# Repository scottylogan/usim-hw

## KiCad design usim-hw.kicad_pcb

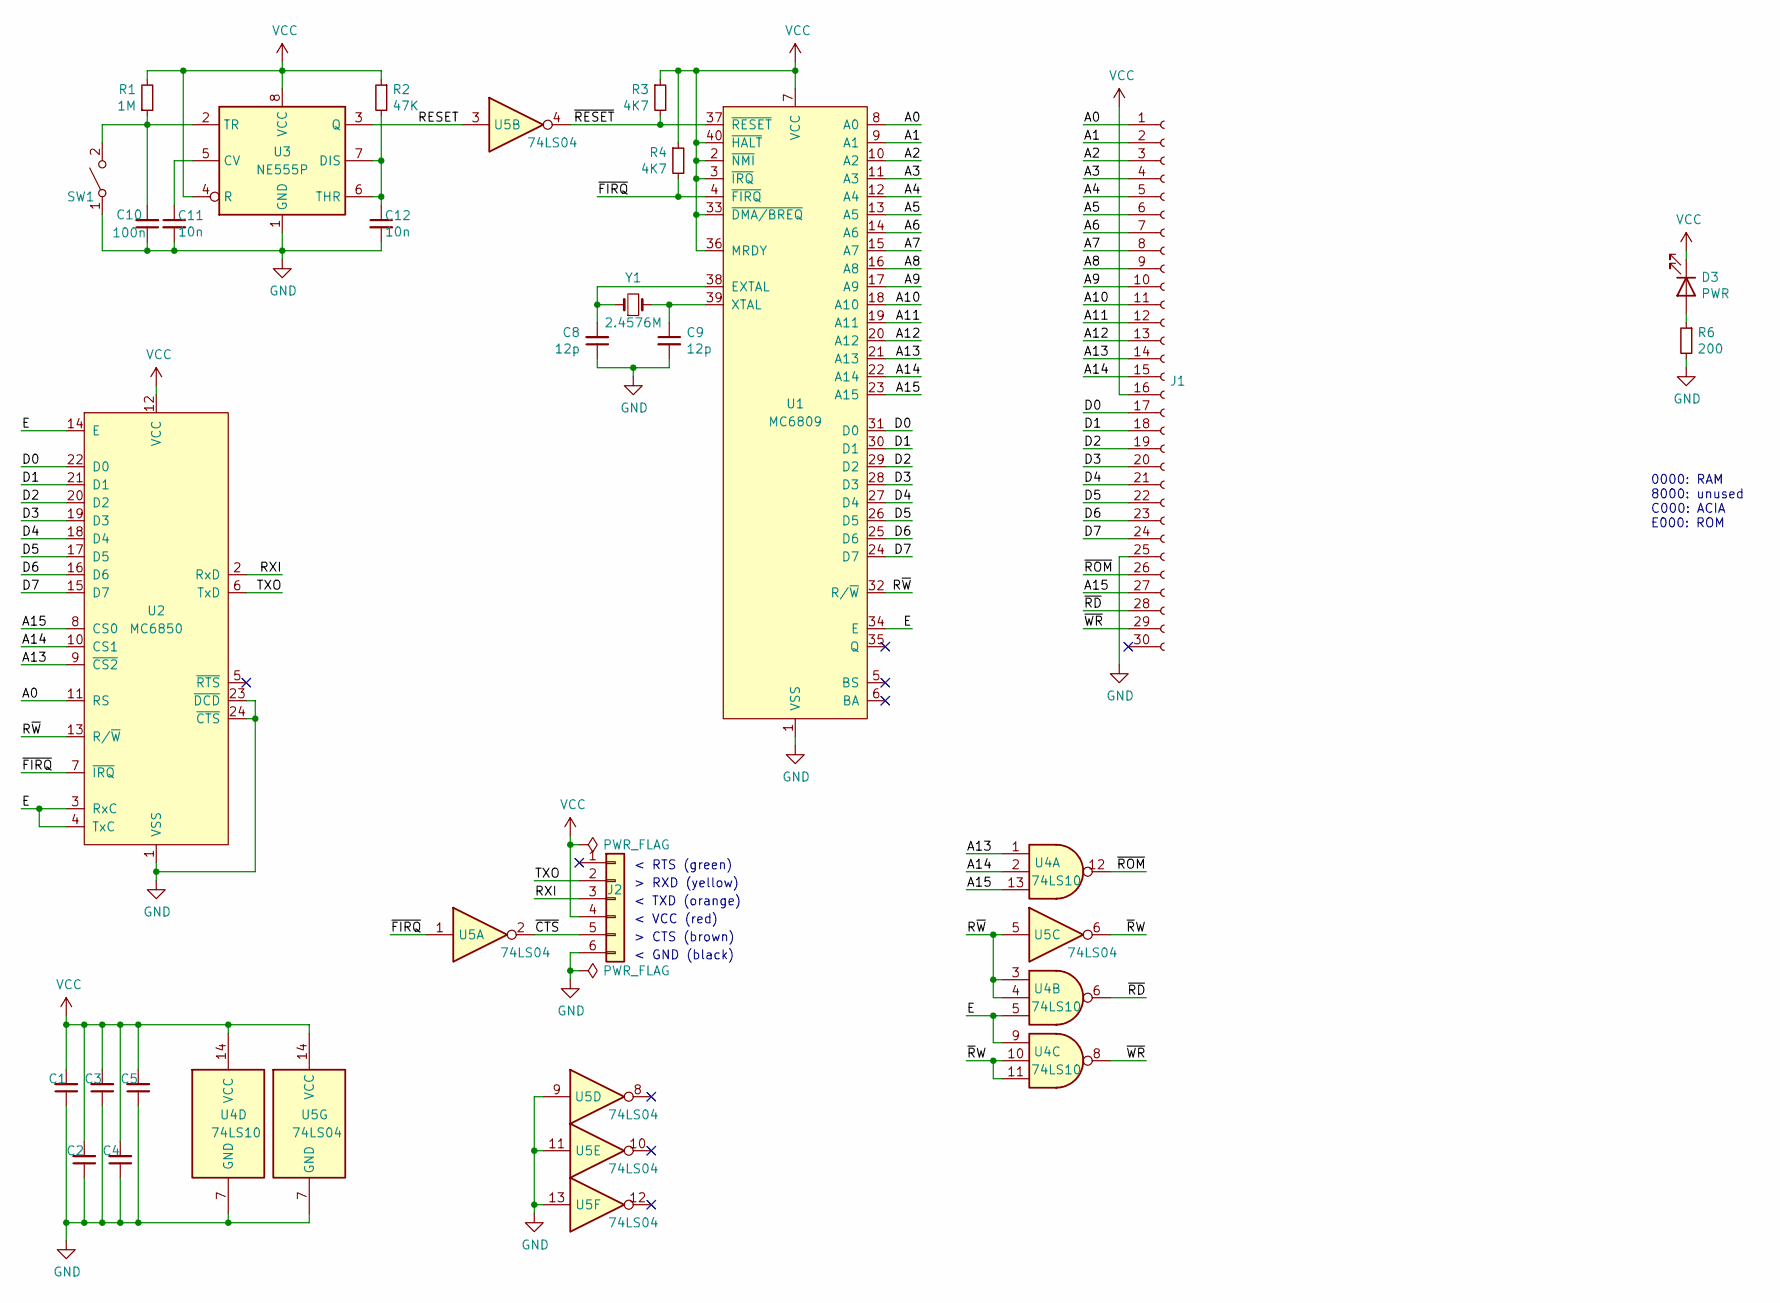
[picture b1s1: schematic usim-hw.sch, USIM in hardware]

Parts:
C1, C2, C3, C4, C5, C10: 100n; C_Disc_D3.0mm_W1.6mm_P2.50mm
C8, C9: 12p; C_Disc_D3.0mm_W1.6mm_P2.50mm
C11, C12: 10n; C_Disc_D3.0mm_W1.6mm_P2.50mm
D3: PWR; LED_D3.0mm
J1: Conn_01x30_Female; PinSocket_1x30_P2.54mm_Vertical
J2: Conn_01x06; PinHeader_1x06_P2.54mm_Vertical
R1: 1M; R_Axial_DIN0204_L3.6mm_D1.6mm_P5.08mm_Horizontal
R2: 47K; R_Axial_DIN0204_L3.6mm_D1.6mm_P5.08mm_Horizontal
R3, R4: 4K7; R_Axial_DIN0204_L3.6mm_D1.6mm_P5.08mm_Horizontal
R6: 200; R_Axial_DIN0204_L3.6mm_D1.6mm_P5.08mm_Horizontal
SW1: SW_SPST; SW_PUSH_6mm
U1: MC6809; DIP-40_W15.24mm_Socket_LongPads
U2: MC6850; DIP-24_W15.24mm_Socket_LongPads
U3: NE555P; DIP-8_W7.62mm_Socket_LongPads
U4: 74LS10; DIP-14_W7.62mm_Socket_LongPads
U5: 74LS04; DIP-14_W7.62mm_Socket_LongPads
Y1: 2.4576M; Crystal_HC49-U_Vertical

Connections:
/A0: J1.1, U1.8 (A0), U2.11 (RS)
/A1: J1.2, U1.9 (A1)
/A2: J1.3, U1.10 (A2)
/A3: J1.4, U1.11 (A3)
/A4: J1.5, U1.12 (A4)
/A5: J1.6, U1.13 (A5)
/A6: J1.7, U1.14 (A6)
/A7: J1.8, U1.15 (A7)
/A8: J1.9, U1.16 (A8)
/A9: J1.10, U1.17 (A9)
/A10: J1.11, U1.18 (A10)
/A11: J1.12, U1.19 (A11)
/A12: J1.13, U1.20 (A12)
/A13: J1.14, U1.21 (A13), U2.9 (~CS2), U4.1
/A14: J1.15, U1.22 (A14), U2.10 (CS1), U4.2
/A15: J1.27, U1.23 (A15), U2.8 (CS0), U4.13
/D0: J1.17, U1.31 (D0), U2.22 (D0)
/D1: J1.18, U1.30 (D1), U2.21 (D1)
/D2: J1.19, U1.29 (D2), U2.20 (D2)
/D3: J1.20, U1.28 (D3), U2.19 (D3)
/D4: J1.21, U1.27 (D4), U2.18 (D4)
/D5: J1.22, U1.26 (D5), U2.17 (D5)
/D6: J1.23, U1.25 (D6), U2.16 (D6)
/D7: J1.24, U1.24 (D7), U2.15 (D7)
/E: U1.34 (E), U2.3 (RxC), U2.4 (TxC), U2.14 (E), U4.5, U4.9
/RESET: U3.3 (Q), U5.3
/RXI: J2.3, U2.2 (RxD)
/R~W: U1.32 (R/~W), U2.13 (R/~W), U4.3, U4.4, U5.5
/TXO: J2.2, U2.6 (TxD)
/~CTS: J2.5, U5.2
/~FIRQ: R4.2, U1.4 (~FIRQ), U2.7 (~IRQ), U5.1
/~RD: J1.28, U4.6
/~RESET: R3.2, U1.37 (~RESET), U5.4
/~ROM: J1.26, U4.12
/~R~W: U4.10, U4.11, U5.6
/~WR: J1.29, U4.8
GND: C1.1, C2.1, C3.1, C4.1, C5.1, C8.1, C9.2, C10.1, C11.2, C12.2, J1.25, J2.6, R6.2, SW1.1 (A), U1.1 (VSS), U2.1 (VSS), U2.23 (~DCD), U2.24 (~CTS), U3.1 (GND), U4.7 (GND), U5.7 (GND), U5.9, U5.11, U5.13
unnamed: C8.2, U1.38 (EXTAL), Y1.1
unnamed: C9.1, U1.39 (XTAL), Y1.2
unnamed: C10.2, R1.1, SW1.2 (B), U3.2 (TR)
unnamed: C11.1, U3.5 (CV)
unnamed: C12.1, R2.2, U3.6 (THR), U3.7 (DIS)
unnamed: D3.2 (A), R6.1
VCC: C1.2, C2.2, C3.2, C4.2, C5.2, D3.1 (K), J1.16, J2.4, R1.2, R2.1, R3.1, R4.1, U1.2 (~NMI), U1.3 (~IRQ), U1.7 (VCC), U1.33 (~DMA/BREQ), U1.36 (MRDY), U1.40 (~HALT), U2.12 (VCC), U3.4 (R), U3.8 (VCC), U4.14 (VCC), U5.14 (VCC)

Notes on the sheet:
< GND (black)
> CTS (brown)
< VCC (red)
< TXD (orange)
> RXD (yellow)
< RTS (green)
0000: RAM 8000: unused C000: ACIA E000: ROM

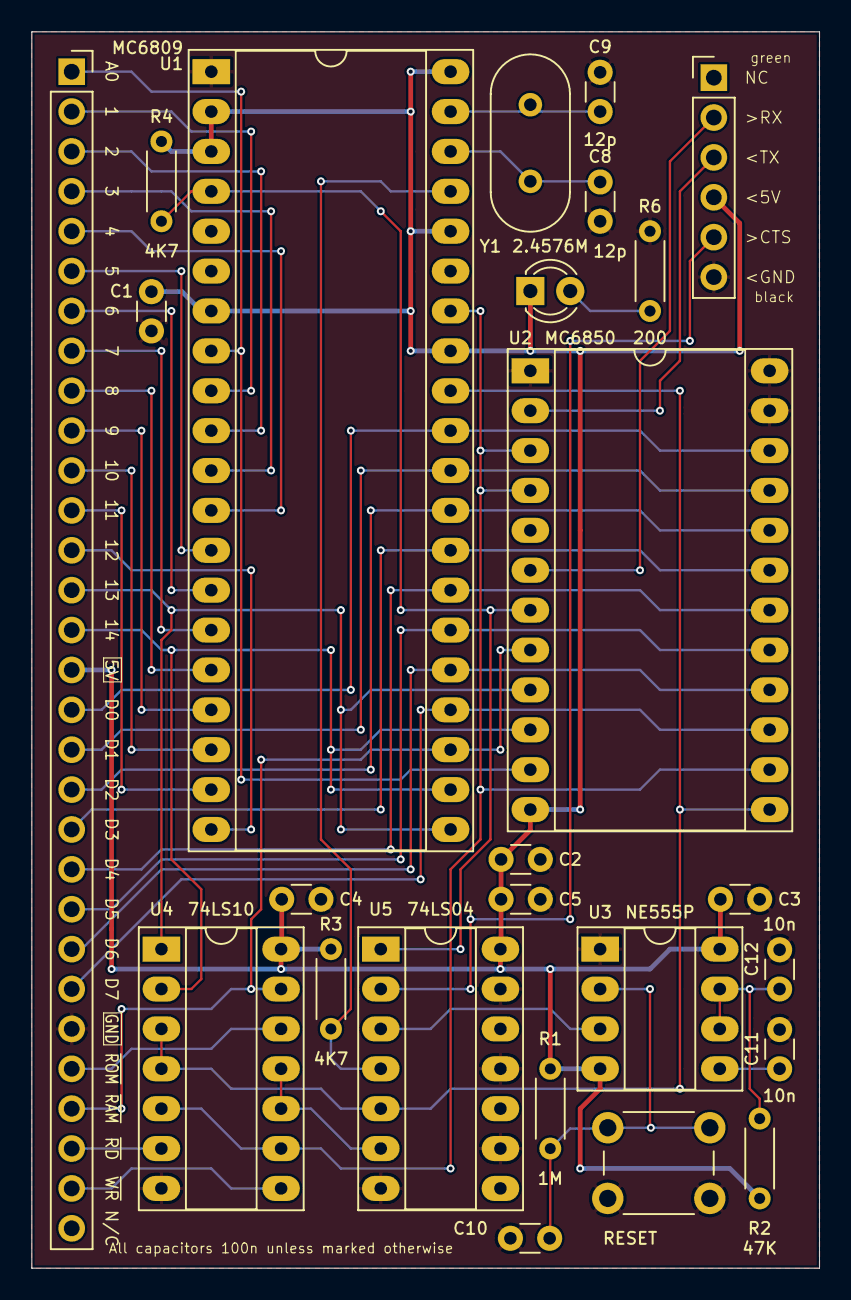
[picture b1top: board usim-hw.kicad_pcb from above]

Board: 2 copper layers, 50.2 x 78.7 mm, 25 parts (0 on the bottom side), 44 nets.

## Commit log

2021-07-22 saved zif-less pcb
2021-07-23 switched to ZIF for EEPROM, shrunk by removing mt. holes
2021-08-05 removed memory to shrink design; use separate memory board
2021-08-05 updated labels
2025-04-16 added LICENSE

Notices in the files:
usim-hw.kicad_pcb:
© 2021, Scotty Logan
